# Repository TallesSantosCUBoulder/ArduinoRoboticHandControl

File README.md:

# Arduino Robotic Hand Control

## Introduction

This project aims to demonstrate the design and construction of a robotic hand capable of mimicking common human hand gestures in real time. The system combines computer vision, Arduino control, servo motors, and 3D printed components to create a robotic hand that responds to hand movements captured by webcam. 

Using OpenCV and MediaPipe, the Python program detects and classifies different hand gestures, then sends the corresponding commands to an Arduino through serial communication. The Arduino controls five SG90 servo motors that move each finger of the robotic hand to replicate the detected gesture. 

This project demonstrates how a few servo motors and simple 3D printed components can be used to create interactive robotic motion.

_Figure 1: Image of fully assembled robotic hand_

## Inspiration & Research

First, I started with a simple Google search for inspiration. I was mainly looking for an existing project with available STL files to avoid redesigning the hand and fingers from scratch. I also wanted a design that used fishing line or cables as finger tendons and was Arduino friendly, since this was discussed with Professor Santos when the project was first assigned.

I found the inspiration for this project on Google Images and chose it because the design seemed simple, used an Arduino, and controlled each finger with SG90 servo motors. I also found additional images from the same project website that showed more detailed views of the assembly process, specifically how the fingers were held together using paracord and where the motors were mounted. The construction looked relatively straightforward, so I proceeded to download the STL files.

Link to Inspiration: https://www.thingiverse.com/thing:4807141/files

## Methodology

### 3D Printing & Finger Movement

- The hand components were printed in PLA filament. Each finger was printed in multiple segments connected with paracord joints to allow realistic bending motion. Fishing line was threaded through channels inside each finger and connected to a servo motor mounted in the forearm so when each servo arm rotates the corresponding finger bends inward.

### Circuit Design

- Each SG90 servo motor was connected to the Arduino using PWM pins. Since multiple servos can draw significant current simultaneously, an external 5V power supply was used instead of powering the servos directly from the Arduino. A 1000 µF capacitor was added across the power rails to reduce voltage drops and servo jitter.

### Gesture Detection

- Python was used with OpenCV and MediaPipe to process webcam video in real time. MediaPipe identifies 21 hand landmarks that represent joints and fingertip locations. The software compares landmark positions to determine whether fingers are extended or bent.

### Serial Communication

- When a gesture is detected, Python sends a simple command string over serial communication to the Arduino. The Arduino interprets the command and adjusts the servo's arm positions to imitate the detected finger positions.

## Hardware

### Basic Materials List
- 1x Arduino Uno
- 5x SG90 Servo Motors
- 200 grams of PLA Filament & 3D Printer
- 1x 5V 2A USB Power Supply
- 1x Spliced USB Cable
- 1x 1000 uF Capacitor
- 5ft of Fishing Line
- 10ft of Paracord
- 5x Rubber Bands

### Additional Materials - Testing
- 1x Breadboard
- 17x Jumper wires

### Printing Process

I modified the STL files from the Thingiverse link above. The arm piece needed to be scaled down to 10% of its original size. After this, I imported the files into my printer's slicer software. For the print settings, I specified auto tree supports, no brim, and 15% infill for the arm, fingers, and arm stand. For the hand, I used the same settings but without supports so that there would be no plastic obstructing the holes where the fishing line will eventually pass through. I oriented the hand and arm in a vertical position, while the fingers were laid flat. Each file was printed separately in case of a misprint.

### Robotic Hand Assembly

#### System Overview

The robotic hand is made up of 3D printed parts, fishing line, rubber bands, and servo motors. The printed parts form the shape of the hand and fingers and keep everything in place. Paracord runs through the fingers to guide how they bend and help them move smoothly. Fishing line connects each finger to a servo motor and acts like a tendon that pulls the fingers closed when the motor turns. Rubber bands help pull the fingers back open after they are bent. The servo motors control the movement by pulling or releasing the fishing line based on electrical signals, allowing each finger to move and form different gestures.

#### Mechanical Component Assembly Instructions

- Remove all supports from the 3D printed parts.
- Cut the paracord and melt one end to make it easier to thread through the holes.
- Starting with the pinky finger, feed the melted end of the paracord up through each segment on the left side of the finger, then back down through the right side, leaving about 6 inches of excess cord on both ends.
- Repeat this process for the ring finger, then continue until all five fingers are threaded.
- Cut the paracord between each finger so each finger has its own separate line.
- Next, cut five pieces of fishing line, each about one foot long. Tie a double fisherman's knot on one end of each line.
- Feed the untied end of the fishing line through the hole at the tip of each finger. The knot should prevent it from pulling through completely.
- Then, route both the paracord and fishing lines through the corresponding holes in the hand piece.
- Tie the paracord for each finger using an overhand knot, leaving about 1 cm of slack between finger segments so they can bend properly.
- Feed the fishing lines from the hand piece into the corresponding holes in the arm piece.
- Secure the bottom of the hand to the top of the arm piece using hot glue.
- Mount five servo motors onto the arm piece using hot glue, positioning them as shown in Figure 2.
- Attach single-sided servo arms to each motor using screws.
- Tie each fishing line to its corresponding servo arm using a double fisherman's knot (see Figure 2).
- Align all servo arms so that when they point toward the top of the hand, the fingers are extended, and when they rotate away from the fingers, the fingers curl into a fist.
- Finally, attach a rubber band to the tip of each finger using a girth hitch. Tie an overhand knot at the base of each finger, leaving a loop large enough to wrap around the paracord knot at the knuckle.

_Figure 2: Image of servo motor configuration & knots - fully opened & closed (side by side)_

_Figure 3: Image of knots on the back of the hand_

_Figure 4: Image of knots on the fingertips_

_Figure 5: Image of wiring coming out of arm_ 

#### Electrical Component Assembly Instructions

- Identify all five servo motors and label them (e.g., Thumb, Index, Middle, Ring, Pinky) to avoid wiring confusion.
- Connect each servo motor to the Arduino:
  - Connect signal wires to separate PWM-capable digital pins.
  - Connect all power (VCC) wires together to a 5V 2A external power supply.
  - Connect all ground (GND) wires together and ensure a common ground between the external power supply and the microcontroller.
  - Place a 1000 µF electrolytic capacitor across the 5V and GND rails near the servos to help smooth current spikes.
- Ensure the ground of the external power supply is connected to the Arduino's ground.
- Organize the cables and glue them to the base of the arm stand piece as shown in Figure 5.
- Upload or connect control code (such as Arduino servo control code) to test each servo individually.
- Calibrate servo positions so that:
  - One direction corresponds to "finger extended"
  - The opposite direction corresponds to "finger curled"

_Figure 6: Circuit Schematic_

_Figure 7: Image of breadboard_

## Software

### System Overview

The software system consists of two programs that work together to detect hand gestures and replicate them on the robotic hand. The Python script runs on a computer and uses the webcam to capture video in real time. Each frame is processed by MediaPipe, which detects 21 hand landmarks and passes them to a gesture recognition function. That function evaluates which fingers are extended or curled and maps the result to one of nine predefined gestures, numbered 1 through 9. Once a new gesture is identified, Python sends the corresponding number to the Arduino over a USB serial connection. The Arduino receives the number, matches it to a switch case, and drives the five servo motors to the positions that replicate that gesture on the robotic hand.

Before running the Python script, the Arduino code must be uploaded and the Arduino IDE serial monitor must be closed. If the serial monitor remains open, the Python script cannot access the COM port and will throw a connection error. After uploading, the Python script is launched from within the Conda virtual environment. The only value that may need to be changed between machines is the serial port name at the top of the Python file. On macOS it appears as `/dev/cu.usbmodemXXXX`, and on Windows it appears as `COMX`, where X is the port number assigned by the operating system. This value can be found in the Arduino IDE under Tools → Port.

The overall software and hardware communication process is shown in Figures 8 and 9.

_Figure 8: System Flowchart (1 of 2)_

_Figure 9: System Flowchart (2 of 2)_

### Arduino Code Explanation

#### Serial Communication & Command Handling

The Arduino is configured to communicate at a baud rate of 115200, which must match the baud rate set in the Python script. In the main `loop()`, the Arduino checks whether data is available on the serial port. When a value arrives, it is read as a string and converted to an integer using `toInt()`. That integer is passed into a `switch` statement that maps each value from 1 to 9 to a specific gesture. Any value outside this range falls into the `default` case, which closes all fingers into a fist position. A 200-millisecond delay is added after each command is processed, and any remaining bytes in the serial buffer are flushed to prevent leftover input from triggering unintended gesture changes.

#### Arduino Library Requirements

The Arduino code uses the built-in `Servo.h` library, which comes pre-installed with the Arduino IDE and does not need to be downloaded separately. No additional libraries are required. It is included at the top of the sketch with:

```cpp
#include <Servo.h>
```

#### Servo Pin Assignments & Initialization

The five servos are attached to PWM-capable digital pins during `setup()`. The pin assignments are as follows:

| Finger | Pin |
| ------ | --- |
| Thumb  | 5   |
| Index  | 6   |
| Middle | 9   |
| Ring   | 10  |
| Pinky  | 11  |

On startup, all servos are moved to the UP (180°) position so the hand begins in a fully open state. The `writeThumbAndMiddle()` function is used for the initial positioning of the thumb and middle finger to ensure the safety logic runs correctly from the start.

#### Servo Position Mapping

Each servo uses two defined positions: `UP` is set to 180 degrees and corresponds to a finger in the extended position, and `DOWN` is set to 0 degrees and corresponds to a finger that is fully curled. These values may need to be adjusted slightly depending on how the fishing line was tensioned and how the servo arms were attached during assembly. The index servo in Gesture 8 is set to 80 degrees rather than a full UP or DOWN position, which places it at a partially bent angle to form a convincing OK shape alongside the pinched thumb.

#### Servo Arm Collision Safety Logic

* The collision safety logic is implemented in two functions: writeThumbSafe() and writeThumbAndMiddle().

  * In writeThumbSafe(), thumb movement is blocked whenever middleIsDown == true, preventing any independent thumb motion that could interfere with the middle finger's position.
  * In writeThumbAndMiddle(), the system performs a similar check using middlePosCurrent == DOWN. If the middle finger is already down, any combined update that would also move the thumb is prevented to avoid unsafe transitions.
* Both functions rely on stored state variables (middleIsDown, middlePosCurrent) to make sure that the thumb is only allowed to move when the middle finger is not in a potentially conflicting position.

`writeThumbSafe()` checks the `middleIsDown` flag before allowing the thumb to move. If the middle finger is currently in the DOWN position, any command to move the thumb to a new position is blocked and a message is printed to the serial monitor. This prevents independent thumb movement while the middle finger is in a position that could cause a collision.

`writeMiddleSafe()` moves the middle servo without restriction but updates the `middleIsDown` flag and the `middlePosCurrent` variable so that subsequent thumb commands can check the current state accurately.

`writeThumbAndMiddle()` handles cases where both servos need to move at the same time. Before executing the move, it checks whether the middle finger is already in the DOWN position and whether the thumb position would actually change. If both conditions are true, the command is blocked. If the middle finger is not down, both servos are moved together and all state variables are updated in a single operation. Moving them together rather than sequentially reduces the window during which one servo could be in an unsafe intermediate position while the other has not yet moved.

### Python Code Explanation

#### Libraries & Environment Setup

Visual Studio Code is used as the development environment to write and run Python code, while Miniconda is used to manage the Python setup and environments. The project uses several libraries, including OpenCV for video capture and image processing, MediaPipe for hand tracking and math for distance calculations.

The Python script depends on the following libraries, all of which must be installed inside the virtual environment before running the script:

| Library | Install Command |
|---|---|
| `opencv-python` | `pip install opencv-python` |
| `mediapipe` | `pip install mediapipe` |
| `pyserial` | `pip install pyserial` |

A dedicated Conda virtual environment was created for this project to isolate its dependencies from other Python projects on the same machine. This prevents version conflicts between libraries and makes the project easier to reproduce. The environment was created using Miniconda with a specific Python version, and all required libraries were installed into it using `pip`. To create and activate the environment, the following commands were run in the terminal:

```bash
conda create -n robothand python=3.9
conda activate robothand
````

All required libraries were then installed into the active environment using `pip`. The environment must be activated each time before running the Python script.

#### MediaPipe & Open CV - Explained

OpenCV handles camera input, image processing, and display, while MediaPipe strictly handles hand tracking and landmark detection.

MediaPipe Hands is a high-fidelity hand and finger tracking solution that employs machine learning to infer 21 three-dimensional landmarks of a hand from a single frame [1]. The system relies on these landmarks, shown in Figure 10, to determine finger positions and compute distances for gesture-based control. The names of these landmarks are shown in Figure 11. The MediaPipe library manages several parameters, including static image mode, maximum number of hands, model complexity, minimum detection confidence, minimum tracking confidence, multi-handedness, and multi-hand landmarks.

_Figure 10: Hand landmark model showing 21 key-points corresponding to 21 hand-knuckle coordinates [1]._

_Figure 11: Hand landmark names indexed from 0 to 20 [1]._

#### Gesture Recognition Logic

The `recognize_gesture()` function receives the 21 MediaPipe landmarks for the detected hand, the handedness label (Left or Right), and the frame dimensions. It evaluates each finger independently before combining the results to identify a gesture.

For the index, middle, ring, and pinky fingers, the function compares the y-coordinate of the fingertip landmark against the y-coordinate of the proximal joint landmark below it. Because image coordinates increase downward, a fingertip with a smaller y-value than its lower joint is above it in the frame, meaning the finger is extended upward. If the fingertip y-value is greater, the finger is curled.

The thumb is handled differently because it moves laterally rather than vertically. Its state is determined by comparing the x-coordinate of the thumb tip against the x-coordinate of the joint below it. The comparison is also flipped depending on whether the hand is labeled Left or Right, since the thumb points in opposite horizontal directions for each hand.

A pinch detection check is also included to handle the OK gesture. The Euclidean distance between the thumb tip and index tip is computed using the `distance()` function shown in Equation 1, and then divided by the distance between the wrist and the base of the middle finger to produce a normalized pinch ratio. This normalization corrects for the hand moving closer to or farther from the camera. If the ratio falls below 0.35, a pinch is registered. The order of the gesture checks in the function matters: the pinch check runs first so that the OK gesture is not misclassified as a different finger combination.

```math
d = \sqrt{(x_2 - x_1)^2 + (y_2 - y_1)^2}
```

<p align="right"><em>Equation 1: Distance Equation</em></p>

A message is also displayed to instruct the user to keep the palm of the hand normal to the camera, since the distance between the fingers is calculated using two-dimensional coordinates. Rotating the fingers so that they overlap can cause the distance to shrink to zero from the camera's perspective.

Once the finger states are evaluated, they are compared against the fixed patterns below to determine which gesture number to send to the Arduino:

| Number Sent | Gesture       | Thumb | Index | Middle | Ring | Pinky |
| ----------- | ------------- | ----- | ----- | ------ | ---- | ----- |
| 1           | One           | Down  | Up    | Down   | Down | Down  |
| 2           | Peace         | Down  | Up    | Up     | Down | Down  |
| 3           | Three         | Down  | Up    | Up     | Up   | Down  |
| 4           | Four          | Down  | Up    | Up     | Up   | Up    |
| 5           | Open Hand     | Up    | Up    | Up     | Up   | Up    |
| 6           | Hang Loose    | Up    | Down  | Down   | Down | Up    |
| 7           | I Love You    | Up    | Up    | Down   | Down | Up    |
| 8           | OK            | Down  | Down  | Up     | Up   | Up    |

The `last_sent` variable is used to prevent the same gesture number from being transmitted repeatedly on consecutive frames. A new serial command is only sent when the recognized gesture differs from the previously sent value, which reduces unnecessary traffic over the serial connection and prevents the Arduino from processing redundant inputs.

IMPORTANT: When running the two scripts, the Arduino script must be uploaded and running first. Once uploaded, close the Serial Monitor in the Arduino IDE to release the serial port. If the Serial Monitor is left open, the Python script will be unable to connect and will throw a connection error. After closing it, run the Python script to begin gesture detection.

## Results

_Figure 12: GIF of mimicked counting gestures being performed_

_Figure 13: GIF of mimicked "hang loose" gesture being performed_

_Figure 14: GIF of mimicked "OK" gesture being performed_

_Figure 15: GIF of mimicked "love you" gesture being performed_

## Conclusion

This project successfully demonstrated that a 3D printed robotic hand can replicate common human hand gestures in real time using a small number of affordable components. By combining MediaPipe's hand landmark detection with Arduino-controlled servo motors and serial communication, the system was able to recognize nine distinct gestures and translate them into physical finger movements with reasonable accuracy and low latency. The mechanical assembly, while straightforward in concept, required careful calibration of servo arm positions and fishing line tension to achieve clean and consistent finger motion. Overall, the project met its core objective of building an interactive robotic hand and served as a practical introduction to the integration of computer vision, embedded systems, and mechanical design.

## References

<table>
<tr>
<td valign="top">[1]</td>
<td>
Google, <i>MediaPipe Hands</i>, MediaPipe Documentation, 2023.<br>
Available: https://developers.google.com/mediapipe/solutions/vision/hand_landmarker
</td>
</tr>
</table>

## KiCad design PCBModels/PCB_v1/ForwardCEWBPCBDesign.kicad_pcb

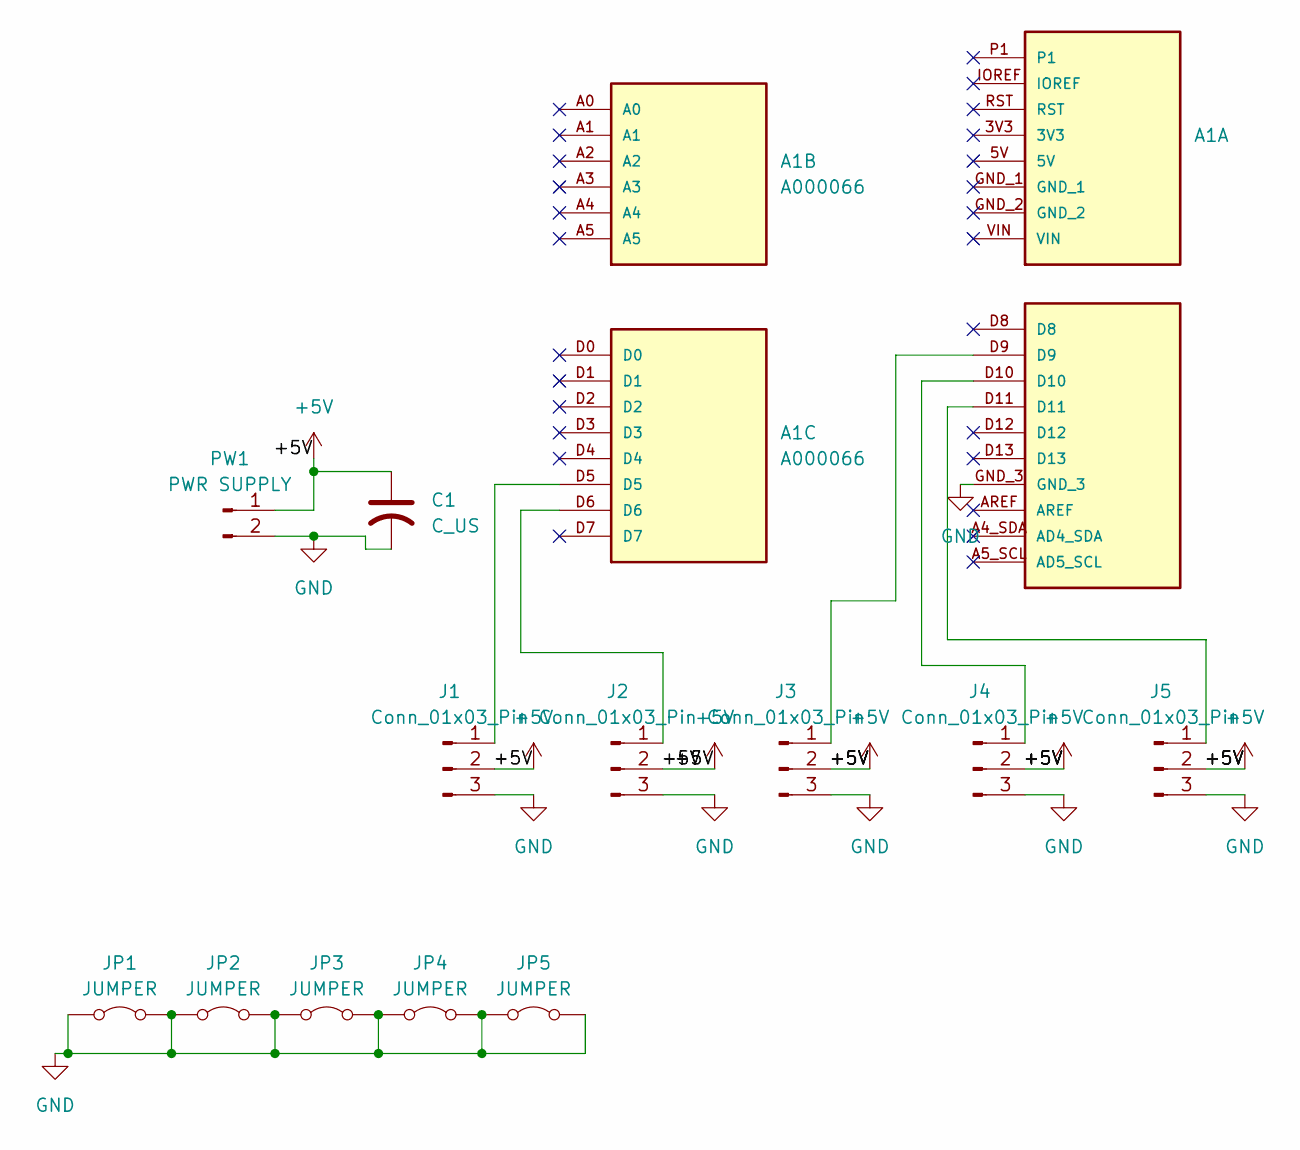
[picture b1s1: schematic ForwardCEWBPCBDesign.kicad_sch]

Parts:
A1: A000066; ARDUINO_A000066
C1: C_US; CP_Radial_D12.5mm_P5.00mm
J1, J2, J3, J4, J5: Conn_01x03_Pin; PinHeader_1x03_P2.54mm_Vertical
JP1, JP2, JP3, JP4, JP5: JUMPER; R_Axial_DIN0207_L6.3mm_D2.5mm_P10.16mm_Horizontal
PW1: PWR SUPPLY; PinHeader_1x02_P2.54mm_Vertical

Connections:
+5V: C1.1, J1.2, J2.2, J3.2, J4.2, J5.2, PW1.1
GND: A1.GND_3, C1.2, J1.3, J2.3, J3.3, J4.3, J5.3, JP1.1 (A), JP1.2 (B), JP2.1 (A), JP2.2 (B), JP3.1 (A), JP3.2 (B), JP4.1 (A), JP4.2 (B), JP5.1 (A), JP5.2 (B), PW1.2
unnamed: A1.D5, J1.1
unnamed: A1.D6, J2.1
unnamed: A1.D9, J3.1
unnamed: A1.D10, J4.1
unnamed: A1.D11, J5.1

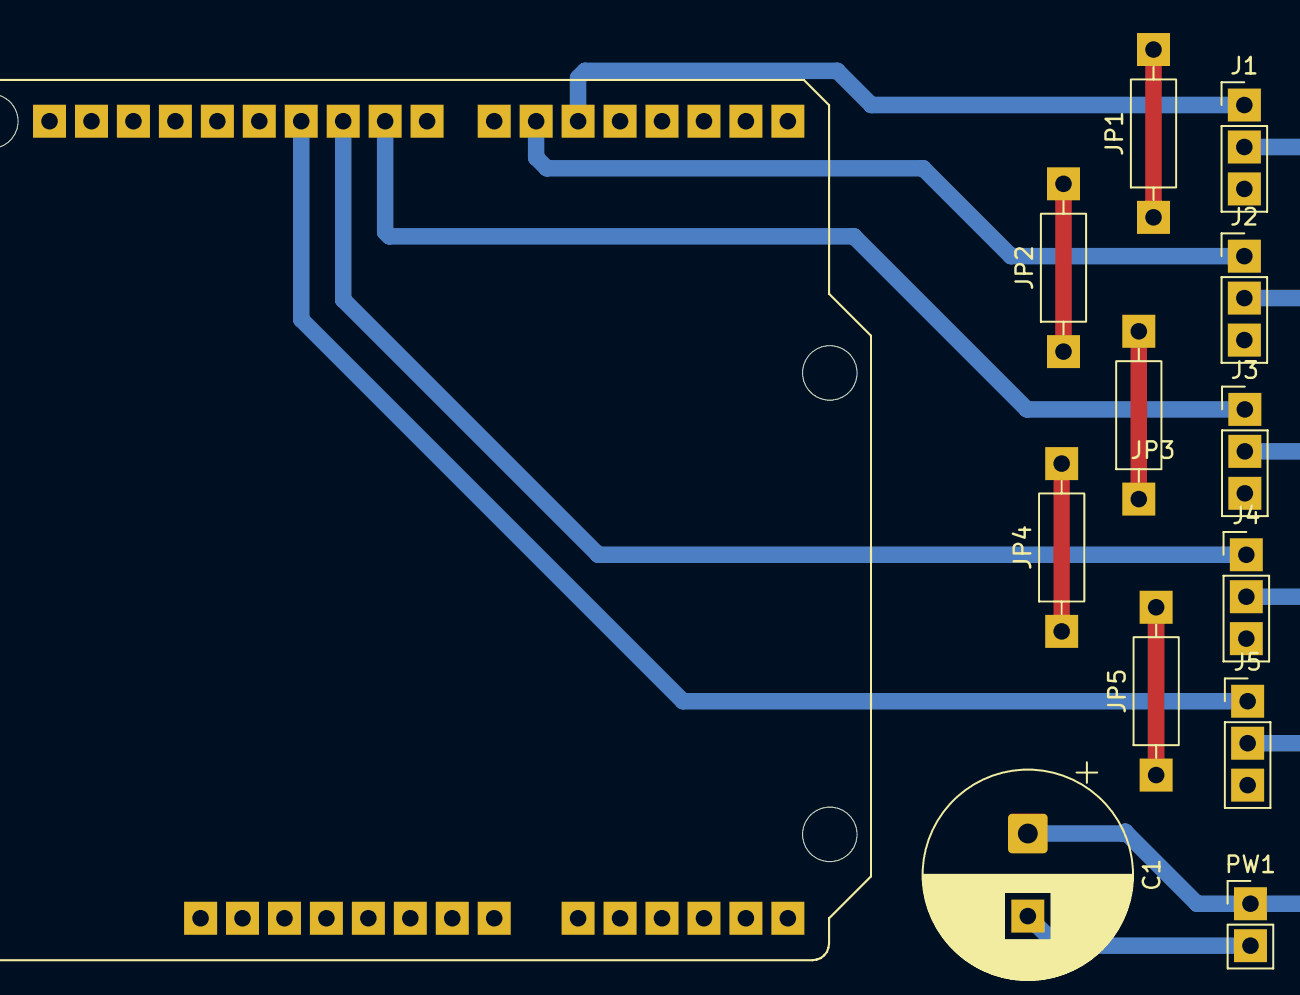
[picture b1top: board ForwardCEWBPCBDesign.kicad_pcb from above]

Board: 2 copper layers, 13 parts (0 on the bottom side), 7 nets.

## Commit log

2026-04-28 PCB example.
2026-04-28 PCB V1.
2026-05-05 Staring the project. Example to Joshua.
2026-05-06 Copied previous README format
2026-05-06 Update README.md
    Added Intro
2026-05-06 Moved files
2026-05-08 Rename DRAFT.md to README.md
2026-05-09 Update README.md
    Moving to google doc
